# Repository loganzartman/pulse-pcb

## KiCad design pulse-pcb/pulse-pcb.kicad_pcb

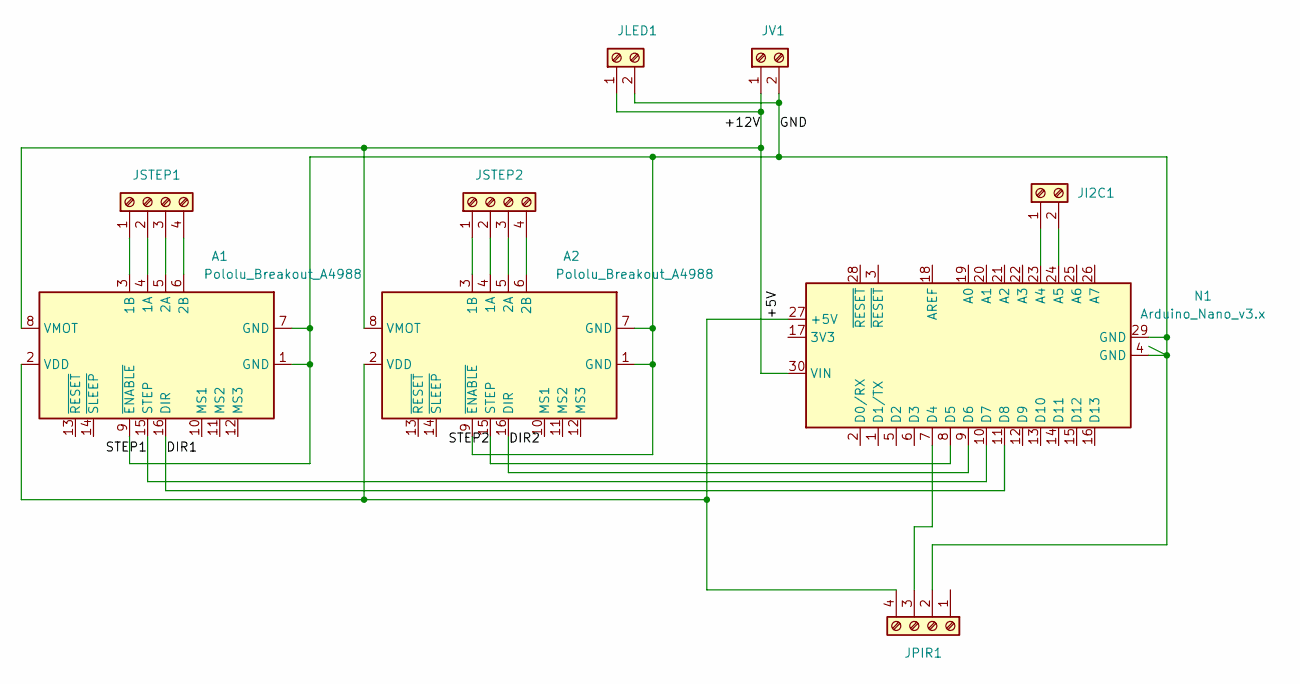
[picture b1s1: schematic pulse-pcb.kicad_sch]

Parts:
A1, A2: Pololu_Breakout_A4988; Pololu_Breakout-16_15.2x20.3mm
JI2C1: Screw_Terminal_01x02; TerminalBlock_bornier-2_P5.08mm
JLED1: Screw_Terminal_01x02; TerminalBlock_bornier-2_P5.08mm
JPIR1: Screw_Terminal_01x04; TerminalBlock_bornier-4_P5.08mm
JSTEP1, JSTEP2: Screw_Terminal_01x04; TerminalBlock_bornier-4_P5.08mm
JV1: Screw_Terminal_01x02; TerminalBlock_bornier-2_P5.08mm
N1: Arduino_Nano_v3.x; Arduino_Nano

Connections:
/+5V: A1.2 (VDD), A2.2 (VDD), JPIR1.4, N1.27 (+5V)
/+12V: A1.8 (VMOT), A2.8 (VMOT), JLED1.1, JV1.1 (+12V), N1.30 (VIN)
/DIR1: A1.16 (DIR), N1.11 (D8)
/GND: A1.1 (GND), A1.7 (GND), A1.9 (~ENABLE), A2.1 (GND), A2.7 (GND), A2.9 (~ENABLE), JLED1.2, JPIR1.2, JV1.2 (GND), N1.4 (GND), N1.29 (GND)
/STEP1: A1.15 (STEP), N1.10 (D7)
unnamed: A1.3 (1B), JSTEP1.1
unnamed: A1.4 (1A), JSTEP1.2
unnamed: A1.5 (2A), JSTEP1.3
unnamed: A1.6 (2B), JSTEP1.4
unnamed: A2.3 (1B), JSTEP2.1
unnamed: A2.4 (1A), JSTEP2.2
unnamed: A2.5 (2A), JSTEP2.3
unnamed: A2.6 (2B), JSTEP2.4
unnamed: A2.15 (STEP), N1.8 (D5)
unnamed: A2.16 (DIR), N1.9 (D6)
unnamed: JI2C1.1, N1.23 (A4)
unnamed: JI2C1.2, N1.24 (A5)
unnamed: JPIR1.3, N1.7 (D4)

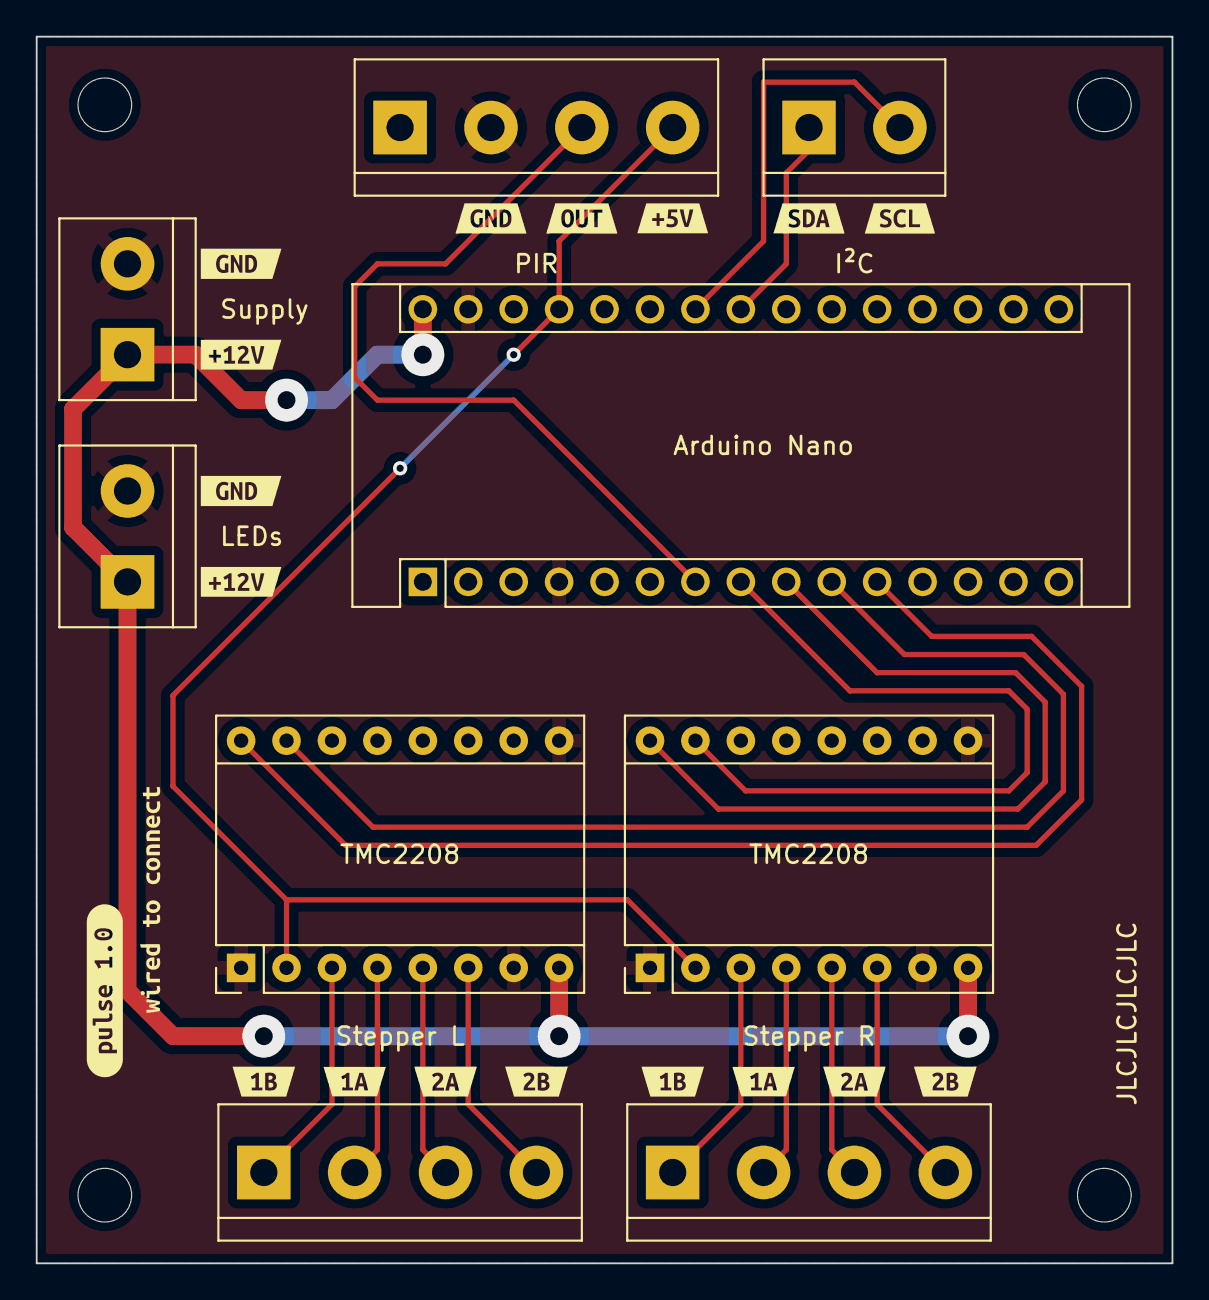
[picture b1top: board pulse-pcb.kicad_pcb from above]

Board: 2 copper layers, 63.5 x 68.6 mm, 28 parts (0 on the bottom side), 18 nets.

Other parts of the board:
kibuzzard-62F38B1C: G***; kibuzzard-62F38B1C
kibuzzard-62F38B4D: G***; kibuzzard-62F38B4D
kibuzzard-62F38B13: G***; kibuzzard-62F38B13
kibuzzard-62F38B54: G***; kibuzzard-62F38B54
kibuzzard-62F38C7F, kibuzzard-62F38C7F#2: G***; kibuzzard-62F38C7F
kibuzzard-62F38C8B, kibuzzard-62F38C8B#2: G***; kibuzzard-62F38C8B
kibuzzard-62F38C83, kibuzzard-62F38C83#2: G***; kibuzzard-62F38C83
kibuzzard-62F38C92, kibuzzard-62F38C92#2: G***; kibuzzard-62F38C92
kibuzzard-62F38DE0: G***; kibuzzard-62F38DE0
kibuzzard-62F38DF4: G***; kibuzzard-62F38DF4
kibuzzard-62F38DFB: G***; kibuzzard-62F38DFB
kibuzzard-62F38E4E: G***; kibuzzard-62F38E4E
kibuzzard-62F38E40: G***; kibuzzard-62F38E40
kibuzzard-62F38F2E: G***; kibuzzard-62F38F2E
kibuzzard-62F38FA3: G***; kibuzzard-62F38FA3

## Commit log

2022-08-10 first
